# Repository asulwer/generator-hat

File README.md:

# generator-hat
Raspberry Pi I2C 8-Channel relay board

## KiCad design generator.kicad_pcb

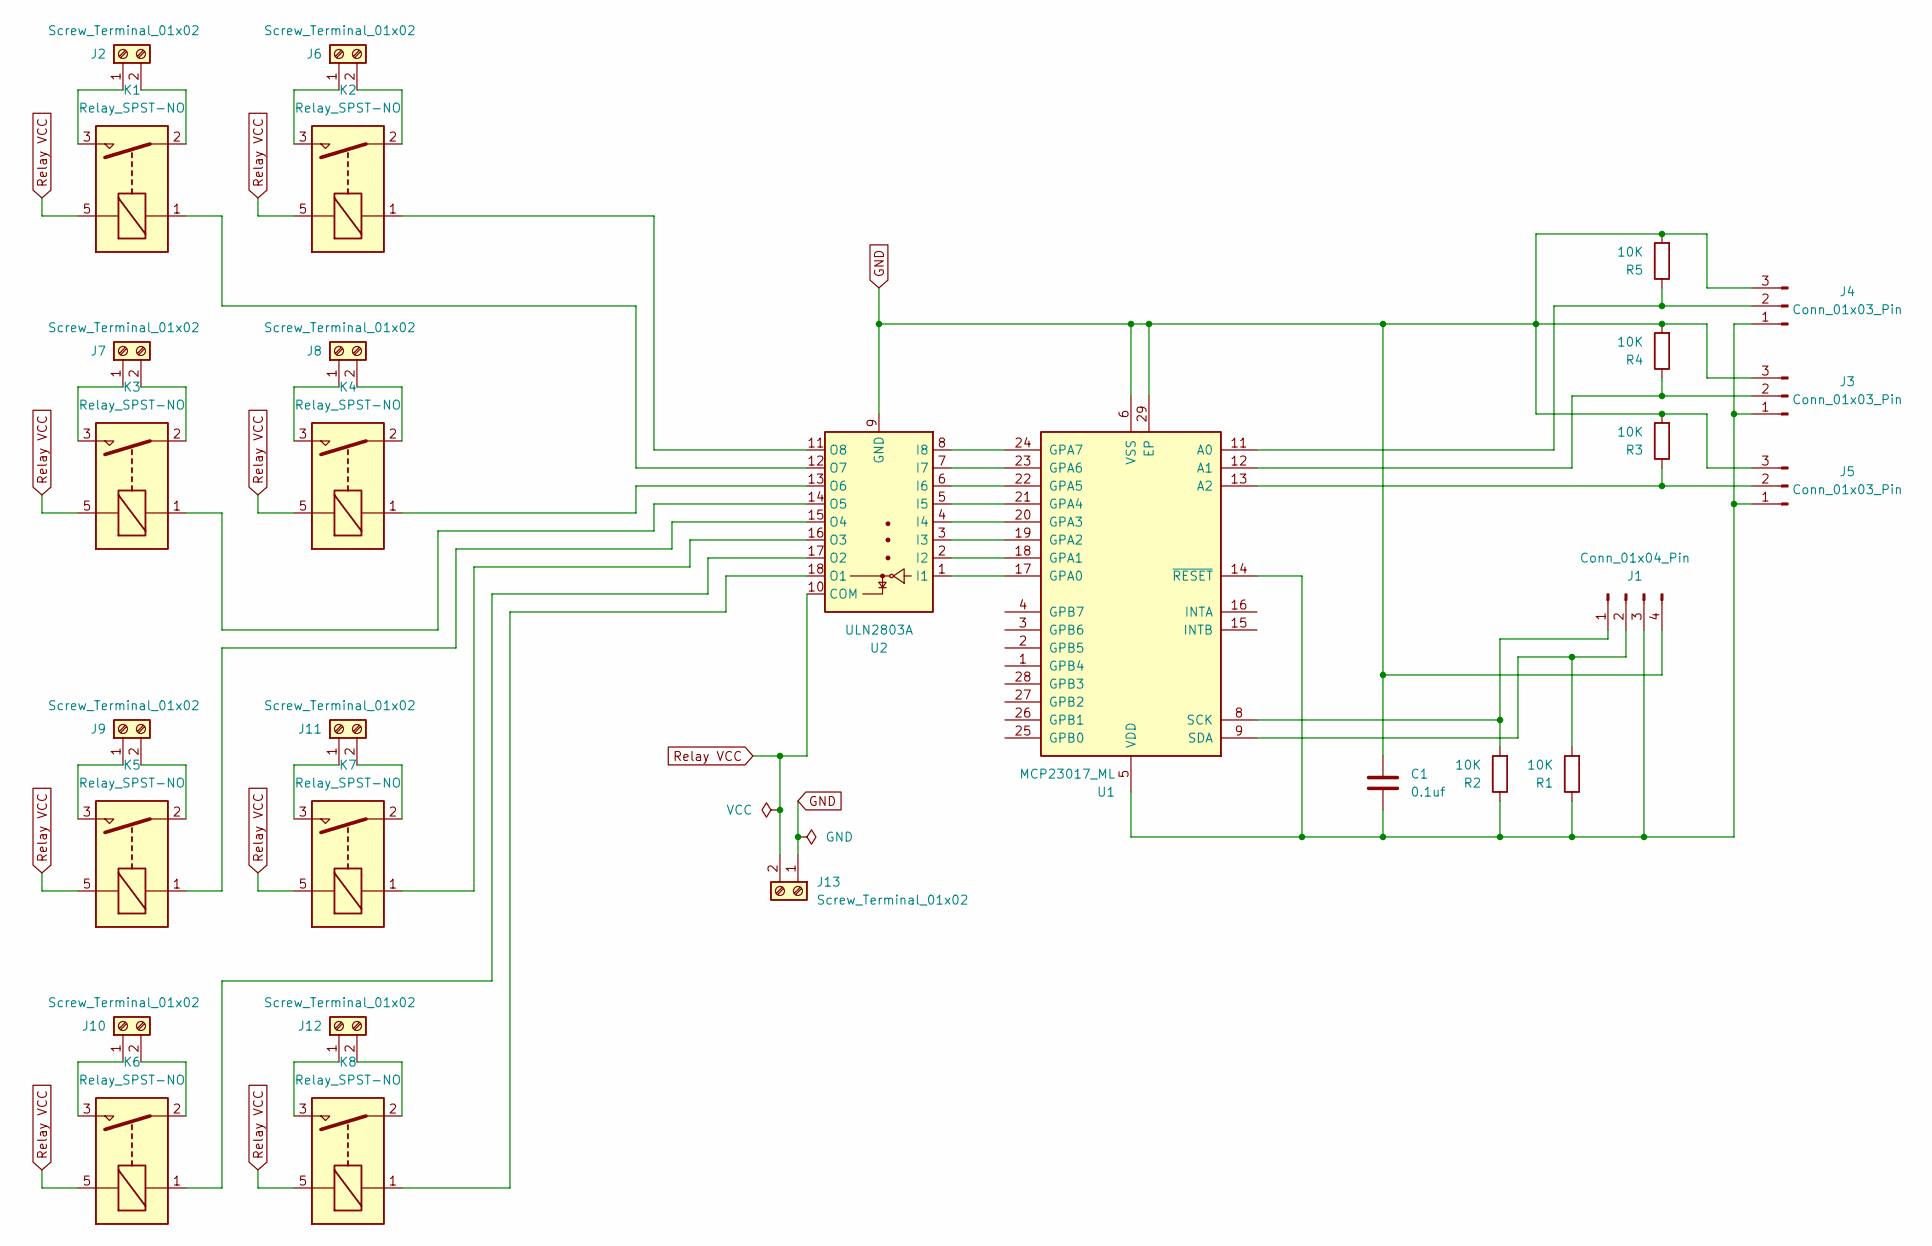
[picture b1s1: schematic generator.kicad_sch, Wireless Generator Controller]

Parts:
C1: 0.1uf; C_0201_0603Metric
J1: Conn_01x04_Pin; PinHeader_1x04_P1.00mm_Vertical
J2, J6, J7, J8, J9, J10, J11, J12, J13: Screw_Terminal_01x02; TerminalBlock_Phoenix_MKDS-1,5-2_1x02_P5.00mm_Horizontal
J3, J4, J5: Conn_01x03_Pin; PinHeader_1x03_P1.00mm_Vertical
K1, K2, K3, K4, K5, K6, K7, K8: Relay_SPST-NO; Relay_SPST_Omron-G5Q-1A
R1, R2, R3, R4, R5: 10K; R_0201_0603Metric
U1: MCP23017_ML; QFN-28-1EP_6x6mm_P0.65mm_EP4.25x4.25mm
U2: ULN2803A; SOIC-18W_7.5x11.6mm_P1.27mm

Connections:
GND: C1.1, J1.4, J3.3, J4.3, J5.3, J13.1, R3.2, R4.2, R5.2, U1.6 (VSS), U1.29 (EP), U2.9 (GND)
unnamed: J1.1, R2.2, U1.8 (SCK)
unnamed: J1.2, R1.2, U1.9 (SDA)
unnamed: C1.2, J1.3, J3.1, J4.1, J5.1, R1.1, R2.1, U1.5 (VDD), U1.14 (~RESET)
unnamed: J2.1, K1.3
unnamed: J2.2, K1.2
unnamed: J3.2, R4.1, U1.12 (A1)
unnamed: J4.2, R5.1, U1.11 (A0)
unnamed: J5.2, R3.1, U1.13 (A2)
unnamed: J6.1, K2.3
unnamed: J6.2, K2.2
unnamed: J7.1, K3.3
unnamed: J7.2, K3.2
unnamed: J8.1, K4.3
unnamed: J8.2, K4.2
unnamed: J9.1, K5.3
unnamed: J9.2, K5.2
unnamed: J10.1, K6.3
unnamed: J10.2, K6.2
unnamed: J11.1, K7.3
unnamed: J11.2, K7.2
unnamed: J12.1, K8.3
unnamed: J12.2, K8.2
unnamed: U1.17 (GPA0), U2.1 (I1)
unnamed: U1.18 (GPA1), U2.2 (I2)
unnamed: U1.19 (GPA2), U2.3 (I3)
unnamed: U1.20 (GPA3), U2.4 (I4)
unnamed: U1.21 (GPA4), U2.5 (I5)
unnamed: U1.22 (GPA5), U2.6 (I6)
unnamed: U1.23 (GPA6), U2.7 (I7)
unnamed: U1.24 (GPA7), U2.8 (I8)
unnamed: K8.1, U2.18 (O1)
unnamed: K6.1, U2.17 (O2)
unnamed: K7.1, U2.16 (O3)
unnamed: K5.1, U2.15 (O4)
unnamed: K3.1, U2.14 (O5)
unnamed: K4.1, U2.13 (O6)
unnamed: K1.1, U2.12 (O7)
unnamed: K2.1, U2.11 (O8)
Relay VCC: J13.2, K1.5, K2.5, K3.5, K4.5, K5.5, K6.5, K7.5, K8.5, U2.10 (COM)

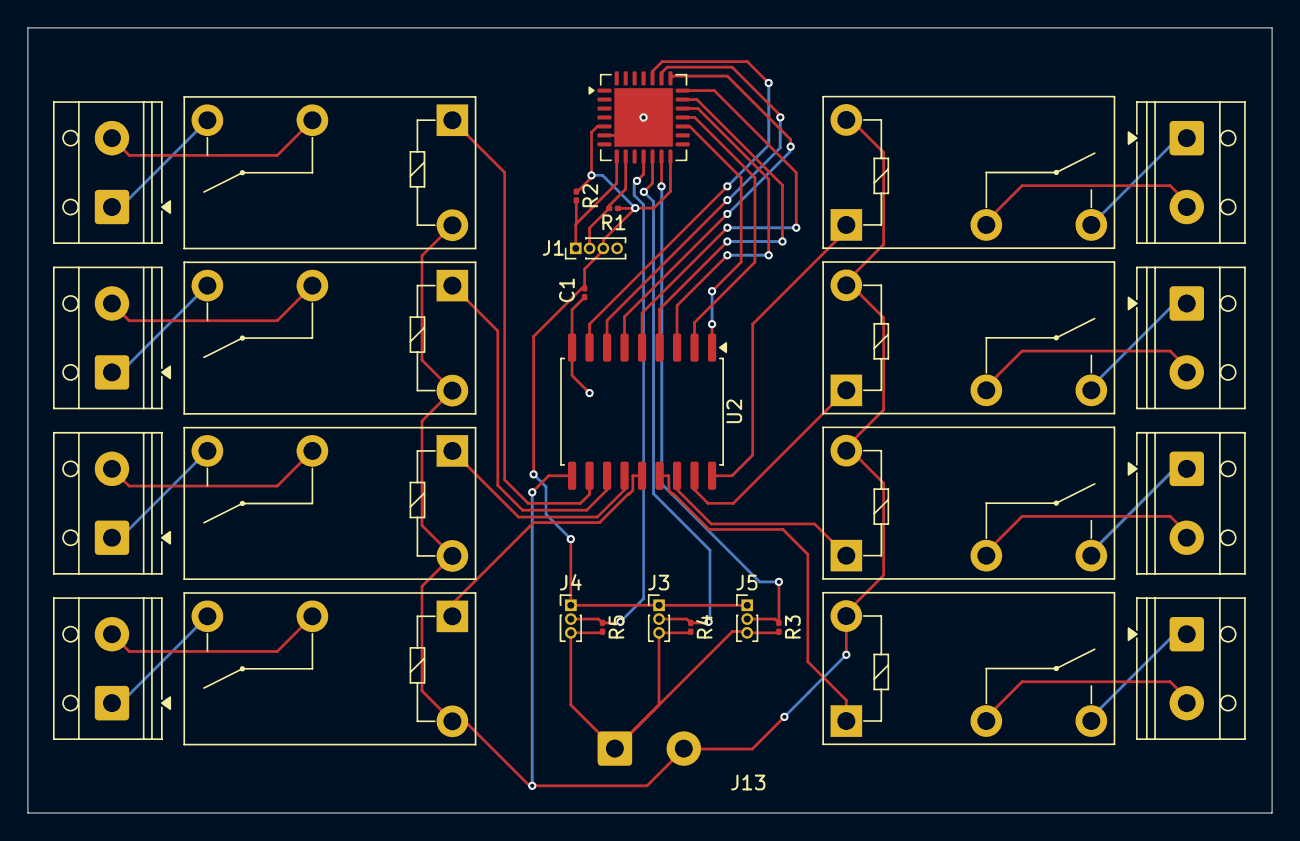
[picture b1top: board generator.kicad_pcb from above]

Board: 2 copper layers, 90.3 x 57.0 mm, 29 parts (1 on the bottom side), 40 nets.

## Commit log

2025-10-25 Add files via upload
    KiCad project files
